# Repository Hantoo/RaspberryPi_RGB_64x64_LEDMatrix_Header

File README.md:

# RaspberryPi_RGB_64x64_LEDMatrix_Header

Simple Raspberry Pi 3/4 header for an RGB 64x64 LED Matrix.  
**Input 5V ONLY!** There is no voltage protection or phase protection. 
For use with LED Matrixes that have A,B,C,D & E selection pins.  
  
Components needed:  
* 2x 74HCT245N  
* 1x Molex , KK 254, 6373, 4 Way, 1 Row, Straight PCB Header, 22-23-2041  
* 1x Molex, KK 254 6373, 2 Way, 1 Row,  Straight PCB Header, 22-23-2021 (**SHOULD BE CHANGED TO CONNECTOR WITH HIGHER LOADING**)  
* 1x 40Pin Raspberry Pi PCB Header  

Connections to raspberry pi follow that of the Adadruit-PWN connection pattern:  
  
    .output_enable = GPIO_BIT(18),  /* Pins 4 and 18 are bound */  
    .clock         = GPIO_BIT(17),  
    .strobe        = GPIO_BIT(21),  
  
    .a             = GPIO_BIT(22),  
    .b             = GPIO_BIT(26),  
    .c             = GPIO_BIT(27),  
    .d             = GPIO_BIT(20),  
    .e             = GPIO_BIT(24),  
  
    .p0_r1         = GPIO_BIT(5),  
    .p0_g1         = GPIO_BIT(13),   
    .p0_b1         = GPIO_BIT(6),  
    .p0_r2         = GPIO_BIT(12),  
    .p0_g2         = GPIO_BIT(16),  
    .p0_b2         = GPIO_BIT(23),  
    
This is the reccomended libary for usage:  
https://github.com/hzeller/rpi-rgb-led-matrix    

Images:

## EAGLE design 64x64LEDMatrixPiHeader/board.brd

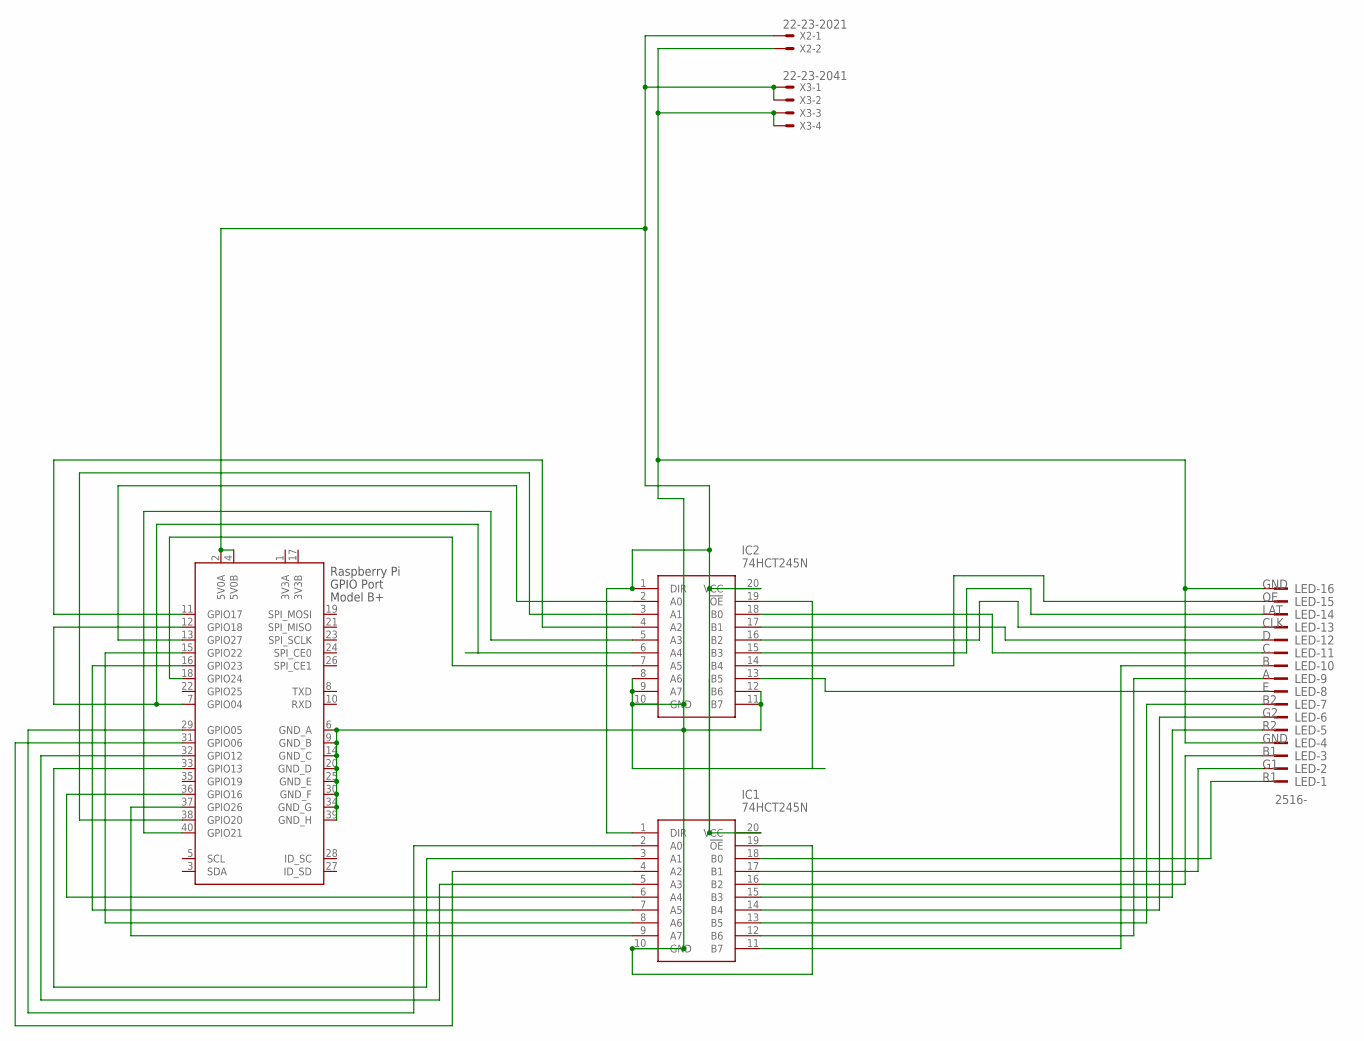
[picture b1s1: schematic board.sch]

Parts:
IC1, IC2: 74HCT245N; DIP762W53P254L2673H420Q20N
LED: 2516-; PAK100/2500-16
X1: RASPI_GPIO_B+#_PIN; RASPI_GPIO_B+_PIN
X2: 22-23-2021
X3: 22-23-2041

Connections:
3V3A: X1.1 (3V3A)
3V3B: X1.17 (3V3B)
+5V: IC1.1 (DIR), IC1.20 (VCC), IC2.1 (DIR), IC2.20 (VCC), X1.2 (5V0A), X1.4 (5V0B), X2.1, X3.1, X3.2
GND: IC1.10 (GND), IC1.19 (!OE), IC2.8 (A6), IC2.9 (A7), IC2.10 (GND), IC2.11 (B7), IC2.12 (B6), IC2.19 (!OE), LED.4, LED.16, X1.6 (GND_A), X1.9 (GND_B), X1.14 (GND_C), X1.20 (GND_D), X1.25 (GND_E), X1.30 (GND_F), X1.34 (GND_G), X1.39 (GND_H), X2.2, X3.3, X3.4
unnamed: IC1.18 (B0), LED.1
unnamed: IC1.17 (B1), LED.2
unnamed: IC1.16 (B2), LED.3
unnamed: IC1.15 (B3), LED.5
unnamed: IC1.14 (B4), LED.6
unnamed: IC1.13 (B5), LED.7
unnamed: IC1.12 (B6), LED.9
unnamed: IC1.11 (B7), LED.10
unnamed: IC2.2 (A0), X1.13 (GPIO27)
unnamed: IC2.18 (B0), LED.11
unnamed: IC2.17 (B1), LED.12
unnamed: IC2.16 (B2), LED.13
unnamed: IC2.15 (B3), LED.14
unnamed: IC2.14 (B4), LED.15
unnamed: IC1.9 (A7), X1.37 (GPIO26)
unnamed: IC2.6 (A4), X1.7 (GPIO04), X1.12 (GPIO18)
unnamed: IC1.7 (A5), X1.16 (GPIO23)
unnamed: IC1.8 (A6), X1.15 (GPIO22)
unnamed: IC2.5 (A3), X1.40 (GPIO21)
unnamed: IC2.3 (A1), X1.38 (GPIO20)
unnamed: IC2.4 (A2), X1.11 (GPIO17)
unnamed: IC1.6 (A4), X1.36 (GPIO16)
unnamed: IC1.3 (A1), X1.33 (GPIO13)
unnamed: IC1.5 (A3), X1.32 (GPIO12)
unnamed: IC1.2 (A0), X1.29 (GPIO05)
unnamed: IC1.4 (A2), X1.31 (GPIO06)
unnamed: IC2.7 (A5), X1.18 (GPIO24)
unnamed: IC2.13 (B5), LED.8

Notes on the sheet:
GND
LAT
CLK

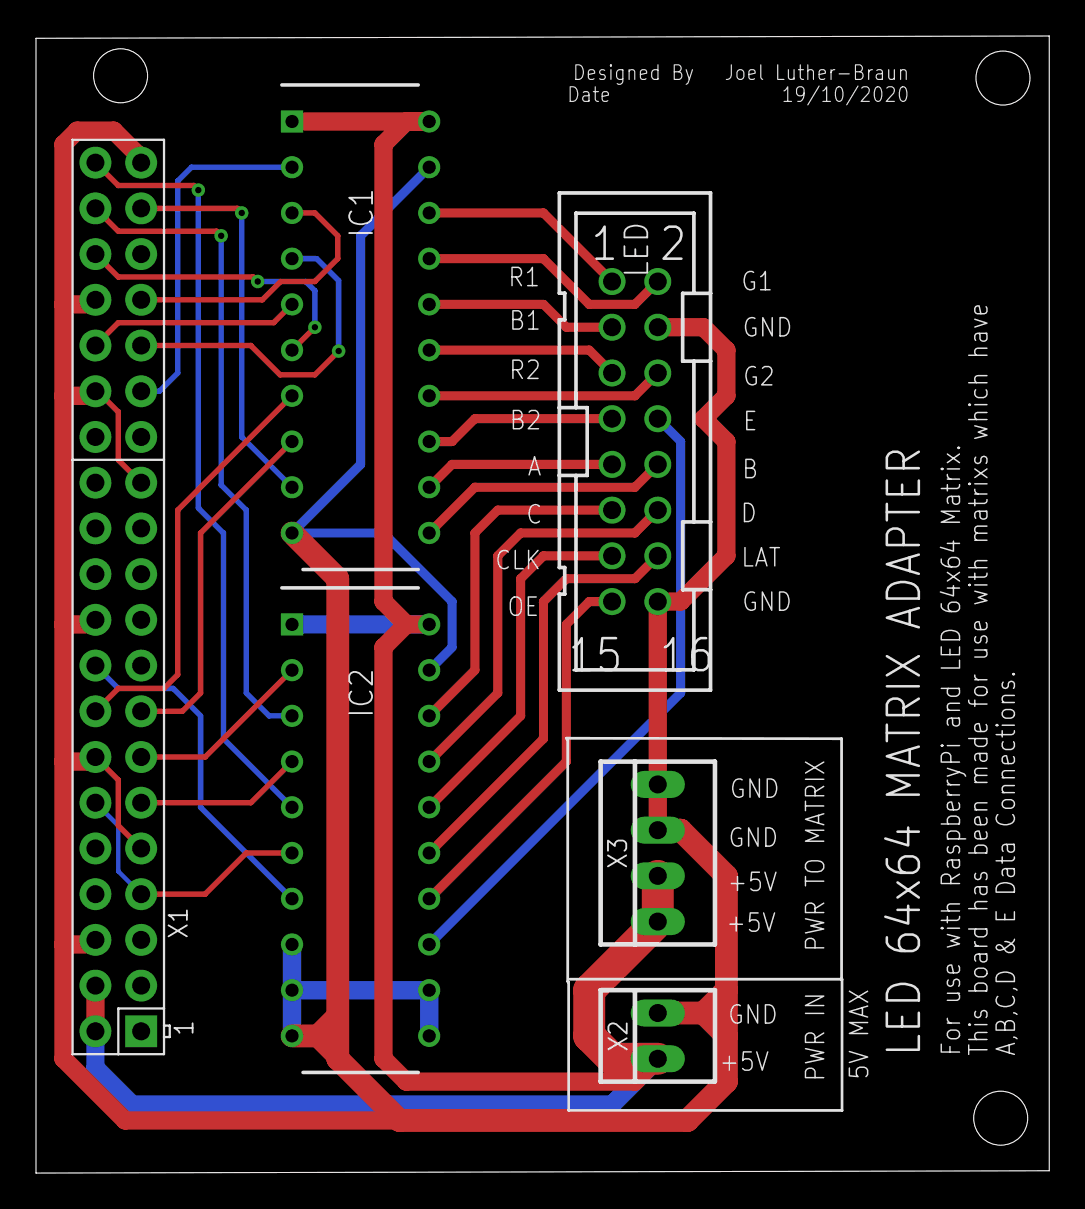
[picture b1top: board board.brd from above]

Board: 2 copper layers, 56.3 x 63.2 mm, 6 parts (0 on the bottom side), 30 nets.
